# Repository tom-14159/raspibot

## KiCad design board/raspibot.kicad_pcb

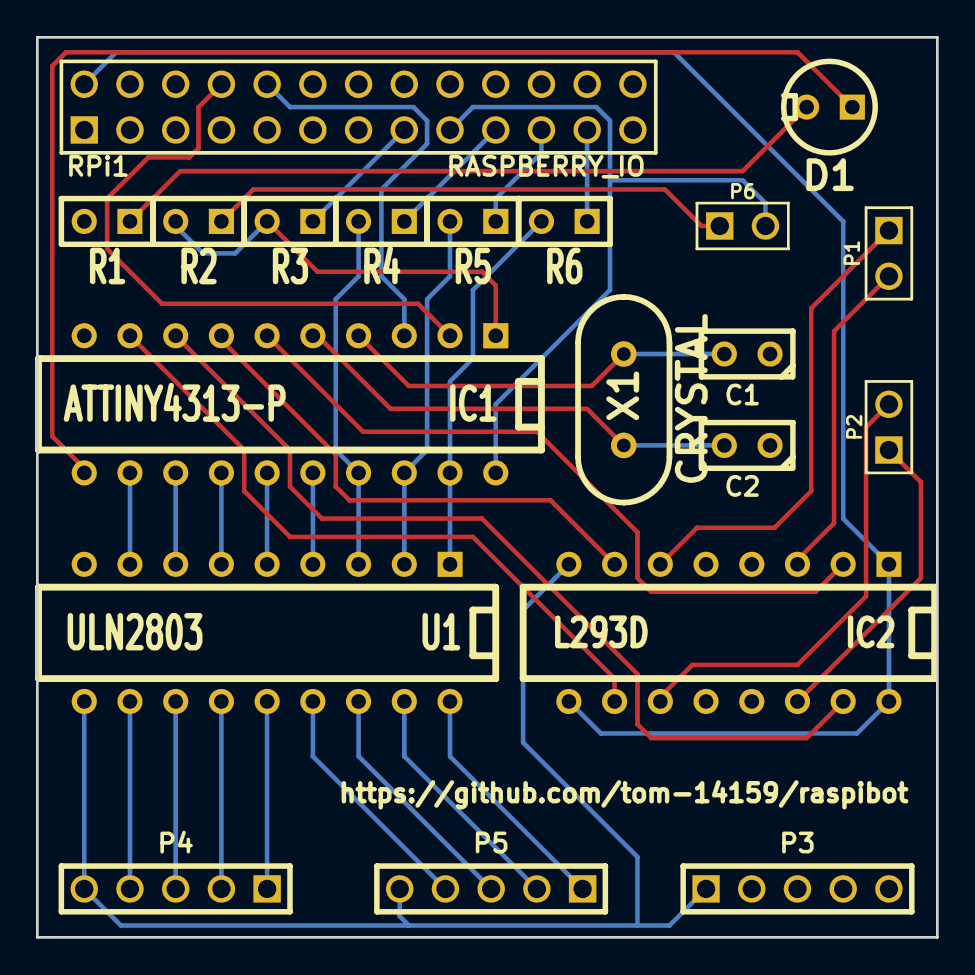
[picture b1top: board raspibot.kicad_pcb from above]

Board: 2 copper layers, 50.0 x 50.0 mm, 20 parts (0 on the bottom side), 40 nets.

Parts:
C1, C2: C; C1
D1: LED; LEDV
IC1: ATTINY4313-P; DIP-20__300
IC2: L293D; DIP-16__300
P1, P2, P6: CONN_2; PIN_ARRAY_2X1
P3, P4, P5: CONN_5; PIN_ARRAY_5x1
R1, R2, R3, R4, R5, R6: R; SIL-2
RPi1: RASPBERRY_IO; pin_array_13x2
U1: ULN2803; DIP-18__300
X1: CRYSTAL; HC-49V

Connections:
GND: C1.1, C2.1, IC1.10, IC2.4, IC2.5, IC2.12, IC2.13, P3.5, R1.2, RPi1.9, RPi1.25, U1.9
unnamed: IC1.7, IC2.7
unnamed: IC1.20, P6.2, RPi1.17
unnamed: IC1.9, IC2.10
unnamed: IC1.8, IC2.15
unnamed: IC1.6, IC2.2
unnamed: D1.1, IC1.11
unnamed: IC1.1, R5.2, R6.2
unnamed: R5.1, RPi1.15
unnamed: IC2.6, P1.1
unnamed: IC2.3, P1.2
unnamed: IC1.3, RPi1.10
unnamed: D1.2, R1.1
unnamed: IC2.14, P2.1
unnamed: IC2.11, P2.2
unnamed: IC1.15, U1.5
unnamed: IC1.16, U1.4
unnamed: IC1.12, U1.8
unnamed: IC1.13, U1.7
unnamed: IC1.14, U1.6
unnamed: P4.4, U1.11
unnamed: IC1.17, R2.2, U1.3
unnamed: R2.1, RPi1.19
unnamed: IC2.8, P3.1, P4.5, P5.5, U1.10
unnamed: P4.3, U1.12
unnamed: P4.2, U1.13
unnamed: P4.1, U1.14
unnamed: P5.3, U1.16
unnamed: P5.2, U1.17
unnamed: P5.1, U1.18
unnamed: P6.1, R6.1
unnamed: IC1.2, RPi1.8
unnamed: IC1.19, R4.2, U1.1
unnamed: IC1.18, R3.2, U1.2
unnamed: R4.1, RPi1.23
unnamed: R3.1, RPi1.21
unnamed: P5.4, U1.15
unnamed: C1.2, IC1.4, X1.2
unnamed: C2.2, IC1.5, X1.1
VCC: IC2.1, IC2.9, IC2.16, RPi1.2

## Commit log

2015-07-21 Plastic motor holder
2015-07-21 Plastic battery holder
2015-07-22 Schematics and netlist for RPi extension board
2015-07-22 Quick and dirty fixes of schematics
    DIRTY!
2015-07-22 Schematics
2015-07-22 Minor fixes, added URL to github repository
